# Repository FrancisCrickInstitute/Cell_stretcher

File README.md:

### Cell sretcher 

### Operation

-	Make sure the PDMS insert is not present!!
-	Connect power supply
-	Press ON/OFF button to ON position (| symbol)
-	The device will “home” all the actuators and move them to the centre
-	Load the PDMS insert
-	Select frequency (Hz)
-	Select stretch (mm)
-	Optional - Press stretch button to change mode (alternative, simultaneous…)
-	Press frequency button to start

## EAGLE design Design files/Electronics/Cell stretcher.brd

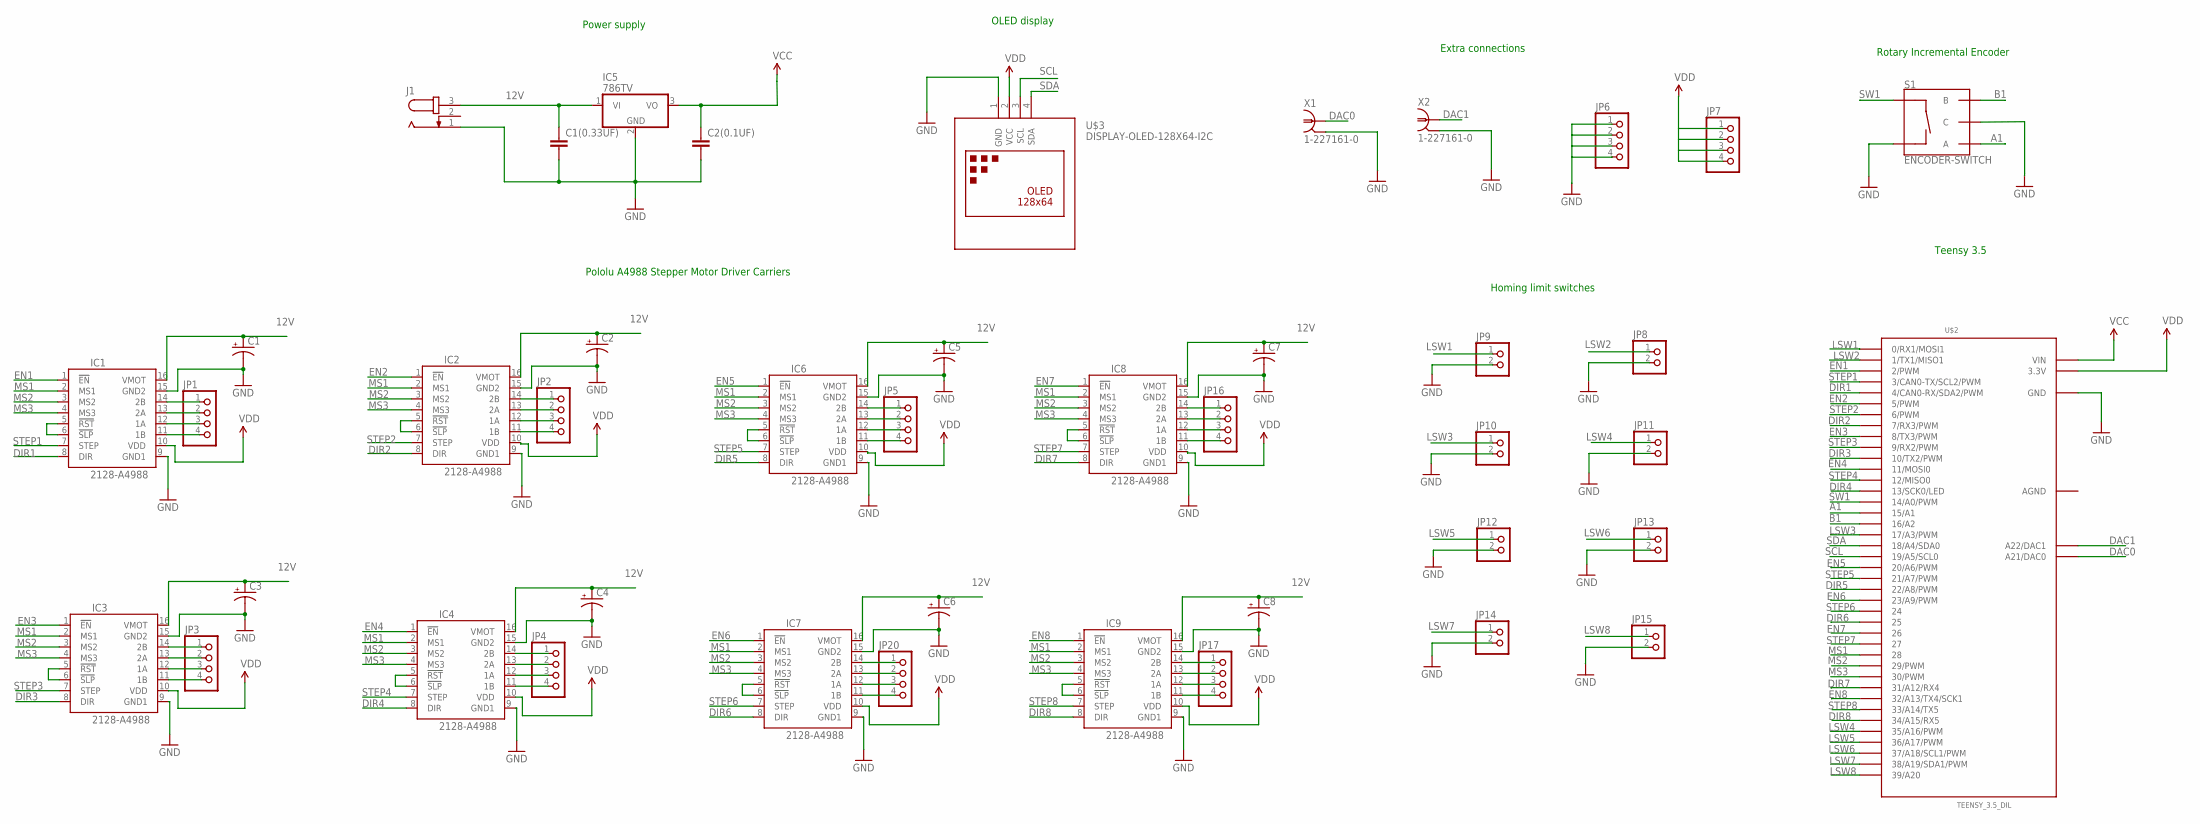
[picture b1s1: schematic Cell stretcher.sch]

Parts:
C1, C2, C3, C4, C5, C6, C7, C8: CPOL-USE5-5; E5-5
C1(0.33UF): C2.5/4; C2.5-4
C2(0.1UF): C2.5/2; C2.5-2
IC1, IC2, IC3, IC4, IC6, IC7, IC8, IC9: 2128-A4988; A4988
IC5: 786TV; TO220V
J1: JACK-PLUG0; SPC4077
JP1, JP2, JP3, JP4, JP5, JP6, JP7, JP16, JP17, JP20: PINHD-1X4; 1X04
JP8, JP9, JP10, JP11, JP12, JP13, JP14, JP15: PINHD-1X2; 1X02
S1: ENCODER-SWITCH; ROTARY_ENC_PLAIN
U$2: TEENSY_3.5_DIL
U$3: DISPLAY-OLED-128X64-I2C
X1, X2: 1-227161-0; AMP_227161

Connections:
12V: C1.+, C1(0.33UF).1, C2.+, C3.+, C4.+, C5.+, C6.+, C7.+, C8.+, IC1.16 (VMOT), IC2.16 (VMOT), IC3.16 (VMOT), IC4.16 (VMOT), IC5.1 (VI), IC6.16 (VMOT), IC7.16 (VMOT), IC8.16 (VMOT), IC9.16 (VMOT), J1.3
A1: S1.A, U$2.15/A1
AGND: U$2.AGND
B1: S1.B, U$2.16/A2
DAC0: U$2.A21 (A21/DAC0), X1.1
DAC1: U$2.A22 (A22/DAC1), X2.1
DIR1: IC1.8 (DIR), U$2.4 (4/CAN0-RX/SDA2/PWM)
DIR2: IC2.8 (DIR), U$2.7 (7/RX3/PWM)
DIR3: IC3.8 (DIR), U$2.10 (10/TX2/PWM)
DIR4: IC4.8 (DIR), U$2.13 (13/SCK0/LED)
DIR5: IC6.8 (DIR), U$2.22/A8 (22/A8/PWM)
DIR6: IC7.8 (DIR), U$2.25
DIR7: IC8.8 (DIR), U$2.31/A12 (31/A12/RX4)
DIR8: IC9.8 (DIR), U$2.34/A15 (34/A15/RX5)
EN1: IC1.1 (!EN), U$2.2 (2/PWM)
EN2: IC2.1 (!EN), U$2.5 (5/PWM)
EN3: IC3.1 (!EN), U$2.8 (8/TX3/PWM)
EN4: IC4.1 (!EN), U$2.11 (11/MOSI0)
EN5: IC6.1 (!EN), U$2.20/A6 (20/A6/PWM)
EN6: IC7.1 (!EN), U$2.23/A9 (23/A9/PWM)
EN7: IC8.1 (!EN), U$2.26
EN8: IC9.1 (!EN), U$2.32/A13 (32/A13/TX4/SCK1)
GND: C1.-, C1(0.33UF).2, C2.-, C2(0.1UF).2, C3.-, C4.-, C5.-, C6.-, C7.-, C8.-, IC1.9 (GND1), IC1.15 (GND2), IC2.9 (GND1), IC2.15 (GND2), IC3.9 (GND1), IC3.15 (GND2), IC4.9 (GND1), IC4.15 (GND2), IC5.2 (GND), IC6.9 (GND1), IC6.15 (GND2), IC7.9 (GND1), IC7.15 (GND2), IC8.9 (GND1), IC8.15 (GND2), IC9.9 (GND1), IC9.15 (GND2), J1.1, JP6.1, JP6.2, JP6.3, JP6.4, JP8.2, JP9.2, JP10.2, JP11.2, JP12.2, JP13.2, JP14.2, JP15.2, S1.C, S1.SW-, U$2.GND, U$2.GND1 (GND), U$3.1 (GND), X1.2, X2.2
LSW1: JP9.1, U$2.0 (0/RX1/MOSI1)
LSW2: JP8.1, U$2.1 (1/TX1/MISO1)
LSW3: JP10.1, U$2.17/A3 (17/A3/PWM)
LSW4: JP11.1, U$2.35/A16 (35/A16/PWM)
LSW5: JP12.1, U$2.36/A17 (36/A17/PWM)
LSW6: JP13.1, U$2.37/A18 (37/A18/SCL1/PWM)
LSW7: JP14.1, U$2.38/A19 (38/A19/SDA1/PWM)
LSW8: JP15.1, U$2.39/A20
MS1: IC1.2 (MS1), IC2.2 (MS1), IC3.2 (MS1), IC4.2 (MS1), IC6.2 (MS1), IC7.2 (MS1), IC8.2 (MS1), IC9.2 (MS1), U$2.28
MS2: IC1.3 (MS2), IC2.3 (MS2), IC3.3 (MS2), IC4.3 (MS2), IC6.3 (MS2), IC7.3 (MS2), IC8.3 (MS2), IC9.3 (MS2), U$2.29 (29/PWM)
MS3: IC1.4 (MS3), IC2.4 (MS3), IC3.4 (MS3), IC4.4 (MS3), IC6.4 (MS3), IC7.4 (MS3), IC8.4 (MS3), IC9.4 (MS3), U$2.30 (30/PWM)
unnamed: IC1.14 (2B), JP1.1
unnamed: IC1.13 (2A), JP1.2
unnamed: IC1.12 (1A), JP1.3
unnamed: IC1.11 (1B), JP1.4
unnamed: IC2.14 (2B), JP2.1
unnamed: IC2.13 (2A), JP2.2
unnamed: IC2.12 (1A), JP2.3
unnamed: IC2.11 (1B), JP2.4
unnamed: IC6.14 (2B), JP5.1
unnamed: IC6.13 (2A), JP5.2
unnamed: IC6.12 (1A), JP5.3
unnamed: IC6.11 (1B), JP5.4
unnamed: IC6.5 (!RST), IC6.6 (!SLP)
unnamed: IC7.14 (2B), JP20.1
unnamed: IC2.5 (!RST), IC2.6 (!SLP)
unnamed: IC7.13 (2A), JP20.2
unnamed: IC7.12 (1A), JP20.3
unnamed: IC7.11 (1B), JP20.4
unnamed: IC7.5 (!RST), IC7.6 (!SLP)
unnamed: IC8.14 (2B), JP16.1
unnamed: IC8.13 (2A), JP16.2
unnamed: IC8.12 (1A), JP16.3
unnamed: IC1.5 (!RST), IC1.6 (!SLP)
unnamed: IC3.14 (2B), JP3.1
unnamed: IC3.13 (2A), JP3.2
unnamed: IC3.12 (1A), JP3.3
unnamed: IC3.11 (1B), JP3.4
unnamed: IC8.11 (1B), JP16.4
unnamed: IC8.5 (!RST), IC8.6 (!SLP)
unnamed: IC9.14 (2B), JP17.1
unnamed: IC9.13 (2A), JP17.2
unnamed: IC9.12 (1A), JP17.3
unnamed: IC9.11 (1B), JP17.4
unnamed: IC9.5 (!RST), IC9.6 (!SLP)
unnamed: IC3.5 (!RST), IC3.6 (!SLP)
unnamed: IC4.14 (2B), JP4.1
unnamed: IC4.13 (2A), JP4.2
unnamed: IC4.12 (1A), JP4.3
unnamed: IC4.11 (1B), JP4.4
unnamed: IC4.5 (!RST), IC4.6 (!SLP)
SCL: U$2.19/A5 (19/A5/SCL0), U$3.3 (SCL)
SDA: U$2.18/A4 (18/A4/SDA0), U$3.4 (SDA)
STEP1: IC1.7 (STEP), U$2.3 (3/CAN0-TX/SCL2/PWM)
STEP2: IC2.7 (STEP), U$2.6 (6/PWM)
STEP3: IC3.7 (STEP), U$2.9 (9/RX2/PWM)
STEP4: IC4.7 (STEP), U$2.12 (12/MISO0)
STEP5: IC6.7 (STEP), U$2.21/A7 (21/A7/PWM)
STEP6: IC7.7 (STEP), U$2.24
STEP7: IC8.7 (STEP), U$2.27
STEP8: IC9.7 (STEP), U$2.33/A14 (33/A14/TX5)
SW1: S1.SW+, U$2.14/A0 (14/A0/PWM)
VCC: C2(0.1UF).1, IC5.3 (VO), U$2.VIN
VDD: IC1.10 (VDD), IC2.10 (VDD), IC3.10 (VDD), IC4.10 (VDD), IC6.10 (VDD), IC7.10 (VDD), IC8.10 (VDD), IC9.10 (VDD), JP7.1, JP7.2, JP7.3, JP7.4, U$2.3.3V, U$2.3.3V3 (3.3V), U$3.2 (VCC)

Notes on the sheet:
Pololu A4988 Stepper Motor Driver Carriers
OLED display
Power supply
Rotary Incremental Encoder
Teensy 3.5
Extra connections
Homing limit switches

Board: 2 copper layers, 43 parts (0 on the bottom side), 86 nets, no tracks yet.

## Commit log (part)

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2022-07-08 Actuator V2
2022-07-14 Mechanical V2
2022-09-01 Electronics schematics
2022-09-12 x4 mould
2022-09-30 Firmware 4 DOF modes
2022-11-08 Step file assembly

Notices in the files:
parts and their libraries:
diy-modules: Released under the Creative Commons Attribution 4.0 International License: http://creativecommons.org/licenses/by/4.0
SparkFun-Switches: Licensing: Creative Commons ShareAlike 4.0 International - https://creativecommons.org/licenses/by-sa/4.0
